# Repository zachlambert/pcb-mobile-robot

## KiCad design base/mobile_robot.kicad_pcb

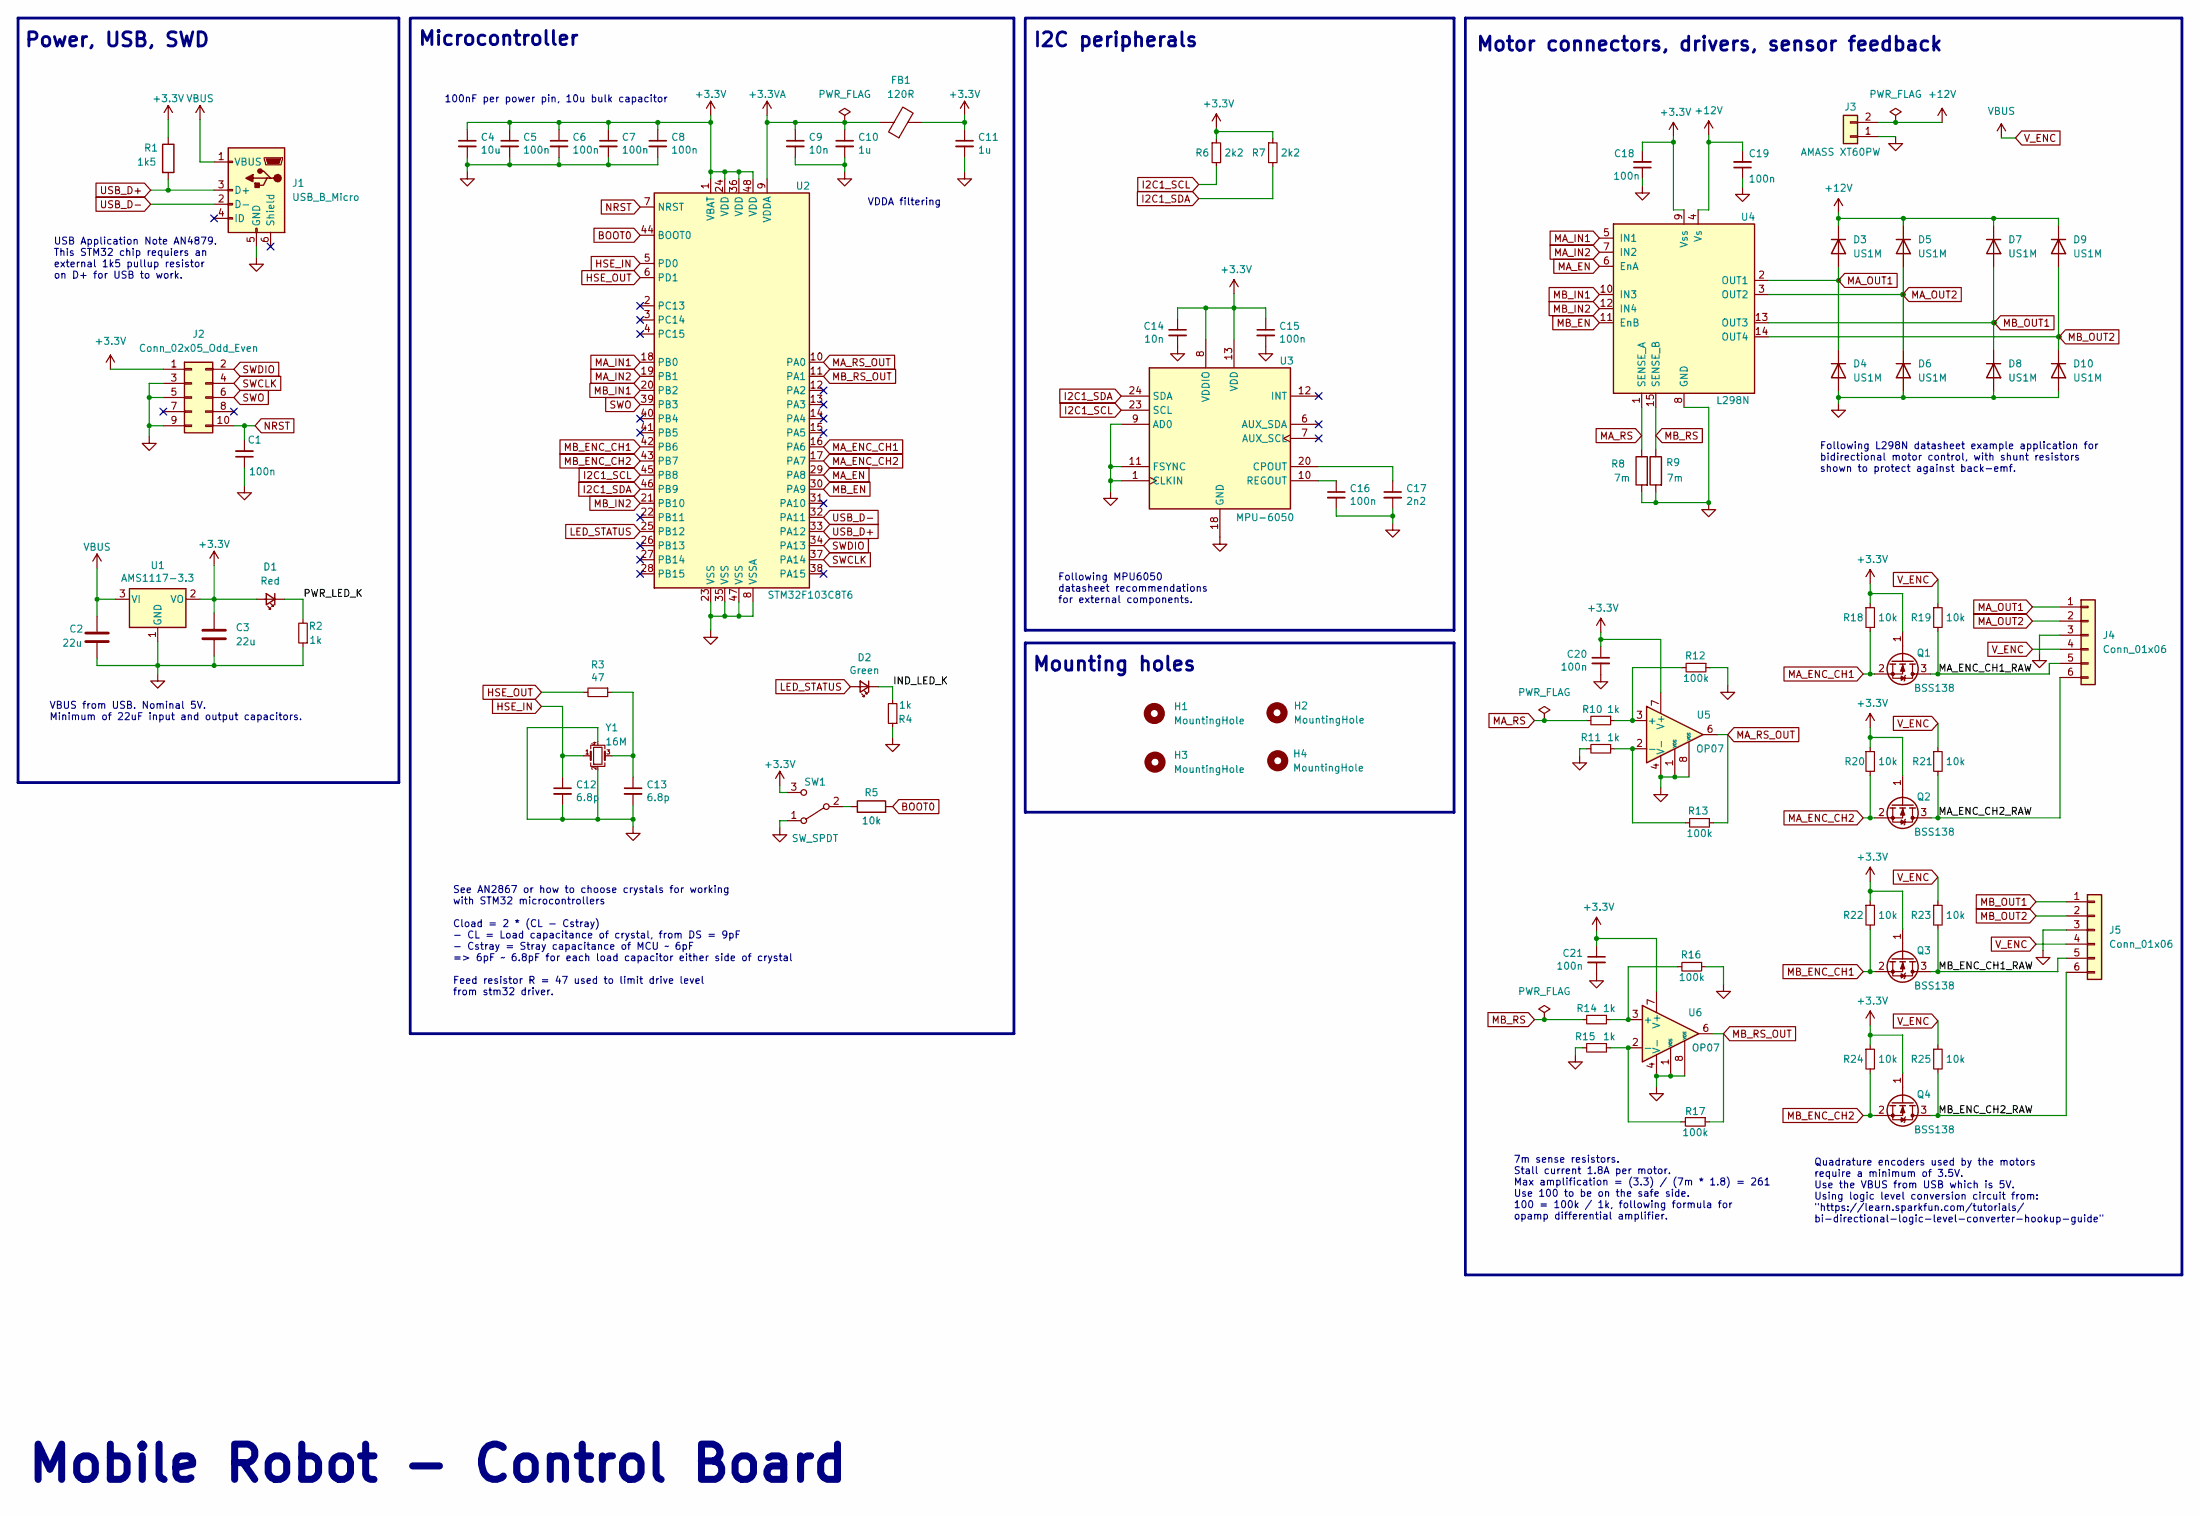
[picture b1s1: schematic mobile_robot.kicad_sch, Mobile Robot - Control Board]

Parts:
C1, C5, C6, C7, C8, C15, C16, C18, C19, C20, C21: 100n; C_0402_1005Metric
C2, C3: 22u; C_0805_2012Metric
C4: 10u; C_0603_1608Metric
C9, C14: 10n; C_0402_1005Metric
C10, C11: 1u; C_0402_1005Metric
C12, C13: 6.8p; C_0402_1005Metric
C17: 2n2; C_0402_1005Metric
D1: Red; D_0603_1608Metric
D2: Green; D_0603_1608Metric
D3, D4, D5, D6, D7, D8, D9, D10: US1M; D_SMA
FB1: 120R; L_0603_1608Metric
H1, H2, H3, H4: MountingHole; MountingHole_3.2mm_M3
J1: USB_B_Micro; USB_Micro-B_Molex_47346-0001
J2: Conn_02x05_Odd_Even; PinHeader_2x05_P2.54mm_Vertical
J3: AMASS XT60PW; AMASS_XT60PW-M
J4, J5: Conn_01x06; PinHeader_1x06_P2.54mm_Vertical
Q1, Q2, Q3, Q4: BSS138; SOT-23
R1: 1k5; R_0402_1005Metric
R2, R4, R10, R11, R14, R15: 1k; R_0402_1005Metric
R3: 47; R_0402_1005Metric
R5, R18, R19, R20, R21, R22, R23, R24, R25: 10k; R_0402_1005Metric
R6, R7: 2k2; R_0402_1005Metric
R8, R9: 7m; R_2512_6332Metric
R12, R13, R16, R17: 100k; R_0402_1005Metric
SW1: SW_SPDT; SW_SPDT_PCM12
U1: AMS1117-3.3; SOT-223-3_TabPin2
U2: STM32F103C8T6; LQFP-48_7x7mm_P0.5mm
U3: MPU-6050; InvenSense_QFN-24_4x4mm_P0.5mm
U4: L298N; TO-220-15_P2.54x2.54mm_StaggerOdd_Lead4.58mm_Vertical
U5, U6: OP07; SOIC-8_3.9x4.9mm_P1.27mm
Y1: 16M; Crystal_SMD_3225-4Pin_3.2x2.5mm

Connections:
+3.3VA: C9.1, C10.1, FB1.1, U2.9 (VDDA)
+3V3: C3.1, C4.1, C5.1, C6.1, C7.1, C8.1, C11.1, C14.1, C15.1, C18.2, C20.1, C21.1, D1.2 (A), FB1.2, J2.1, Q1.1 (G), Q2.1 (G), Q3.1 (G), Q4.1 (G), R1.1, R6.1, R7.1, R18.1, R20.1, R22.1, R24.1, SW1.3 (C), U1.2 (VO), U2.1 (VBAT), U2.24 (VDD), U2.36 (VDD), U2.48 (VDD), U3.8 (VDDIO), U3.13 (VDD), U4.9 (Vss), U5.7 (V+), U6.7 (V+)
+12V: C19.2, D3.1 (K), D5.1 (K), D7.1 (K), D9.1 (K), J3.2, U4.4 (Vs)
/IND_LED_K: D2.1 (K), R4.2
/MA_ENC_CH1_RAW: J4.5, Q1.3 (D), R19.2
/MA_ENC_CH2_RAW: J4.6, Q2.3 (D), R21.2
/MB_ENC_CH1_RAW: J5.5, Q3.3 (D), R23.2
/MB_ENC_CH2_RAW: J5.6, Q4.3 (D), R25.2
/PWR_LED_K: D1.1 (K), R2.2
BOOT0: R5.2, U2.44 (BOOT0)
GND: C1.1, C2.2, C3.2, C4.2, C5.2, C6.2, C7.2, C8.2, C9.2, C10.2, C11.2, C12.2, C13.2, C14.2, C15.2, C16.2, C17.2, C18.1, C19.1, C20.2, C21.2, D4.2 (A), D6.2 (A), D8.2 (A), D10.2 (A), J1.5 (GND), J2.3, J2.5, J2.9, J3.1, J4.3, J5.3, R2.1, R4.1, R8.2, R9.2, R11.2, R12.1, R15.2, R16.1, SW1.1 (A), U1.1 (GND), U2.8 (VSSA), U2.23 (VSS), U2.35 (VSS), U2.47 (VSS), U3.1 (CLKIN), U3.9 (AD0), U3.11 (FSYNC), U3.18 (GND), U4.8 (GND), U5.1 (VOS), U5.4 (V-), U5.8 (VOS), U6.1 (VOS), U6.4 (V-), U6.8 (VOS), Y1.2, Y1.4
HSE_IN: C12.1, U2.5 (PD0), Y1.1
HSE_OUT: R3.2, U2.6 (PD1)
I2C1_SCL: R6.2, U2.45 (PB8), U3.23 (SCL)
I2C1_SDA: R7.2, U2.46 (PB9), U3.24 (SDA)
LED_STATUS: D2.2 (A), U2.25 (PB12)
MA_EN: U2.29 (PA8), U4.6 (EnA)
MA_ENC_CH1: Q1.2 (S), R18.2, U2.16 (PA6)
MA_ENC_CH2: Q2.2 (S), R20.2, U2.17 (PA7)
MA_IN1: U2.18 (PB0), U4.5 (IN1)
MA_IN2: U2.19 (PB1), U4.7 (IN2)
MA_OUT1: D3.2 (A), D4.1 (K), J4.1, U4.2 (OUT1)
MA_OUT2: D5.2 (A), D6.1 (K), J4.2, U4.3 (OUT2)
MA_RS: R8.1, R10.2, U4.1 (SENSE_A)
MA_RS_OUT: R13.1, U2.10 (PA0), U5.6
MB_EN: U2.30 (PA9), U4.11 (EnB)
MB_ENC_CH1: Q3.2 (S), R22.2, U2.42 (PB6)
MB_ENC_CH2: Q4.2 (S), R24.2, U2.43 (PB7)
MB_IN1: U2.20 (PB2), U4.10 (IN3)
MB_IN2: U2.21 (PB10), U4.12 (IN4)
MB_OUT1: D7.2 (A), D8.1 (K), J5.1, U4.13 (OUT3)
MB_OUT2: D9.2 (A), D10.1 (K), J5.2, U4.14 (OUT4)
MB_RS: R9.1, R14.2, U4.15 (SENSE_B)
MB_RS_OUT: R17.1, U2.11 (PA1), U6.6
NRST: C1.2, J2.10, U2.7 (NRST)
unnamed: C13.1, R3.1, Y1.3
unnamed: C16.1, U3.10 (REGOUT)
unnamed: C17.1, U3.20 (CPOUT)
unnamed: R5.1, SW1.2 (B)
unnamed: R10.1, R12.2, U5.3 (+)
unnamed: R11.1, R13.2, U5.2 (-)
unnamed: R14.1, R16.2, U6.3 (+)
unnamed: R15.1, R17.2, U6.2 (-)
SWCLK: J2.4, U2.37 (PA14)
SWDIO: J2.2, U2.34 (PA13)
SWO: J2.6, U2.39 (PB3)
USB_D+: J1.3 (D+), R1.2, U2.33 (PA12)
USB_D-: J1.2 (D-), U2.32 (PA11)
V_ENC: C2.1, J1.1 (VBUS), J4.4, J5.4, R19.1, R21.1, R23.1, R25.1, U1.3 (VI)

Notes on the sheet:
Motor connectors, drivers, sensor feedback
VDDA filtering
Following MPU6050 datasheet recommendations for external components.
I2C peripherals
Mounting holes
100nF per power pin, 10u bulk capacitor
Microcontroller
7m sense resistors. Stall current 1.8A per motor. Max amplification = (3.3) / (7m * 1.8) = 261 Use 100 to be on the safe side. 100 = 100k / 1k, following formula for opamp differential amplifier.
Mobile Robot - Control Board
Power, USB, SWD
Following L298N datasheet example application for bidirectional motor control, with shunt resistors shown to protect against back-emf.
See AN2867 or how to choose crystals for working with STM32 microcontrollers Cload = 2 * (CL - Cstray) - CL = Load capacitance of crystal, from DS = 9pF - Cstray = Stray capacitance of MCU ~ 6pF => 6pF ~ 6.8pF for each load capacitor either side of crystal Feed resistor R = 47 used to limit drive l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
VBUS from USB. Nominal 5V. Minimum of 22uF input and output capacitors.
USB Application Note AN4879. This STM32 chip requiers an external 1k5 pullup resistor on D+ for USB to work.
Quadrature encoders used by the motors require a minimum of 3.5V. Use the VBUS from USB which is 5V. Using logic level conversion circuit from: "https://learn.sparkfun.com/tutorials/ bi-directional-logic-level-converter-hookup-guide"

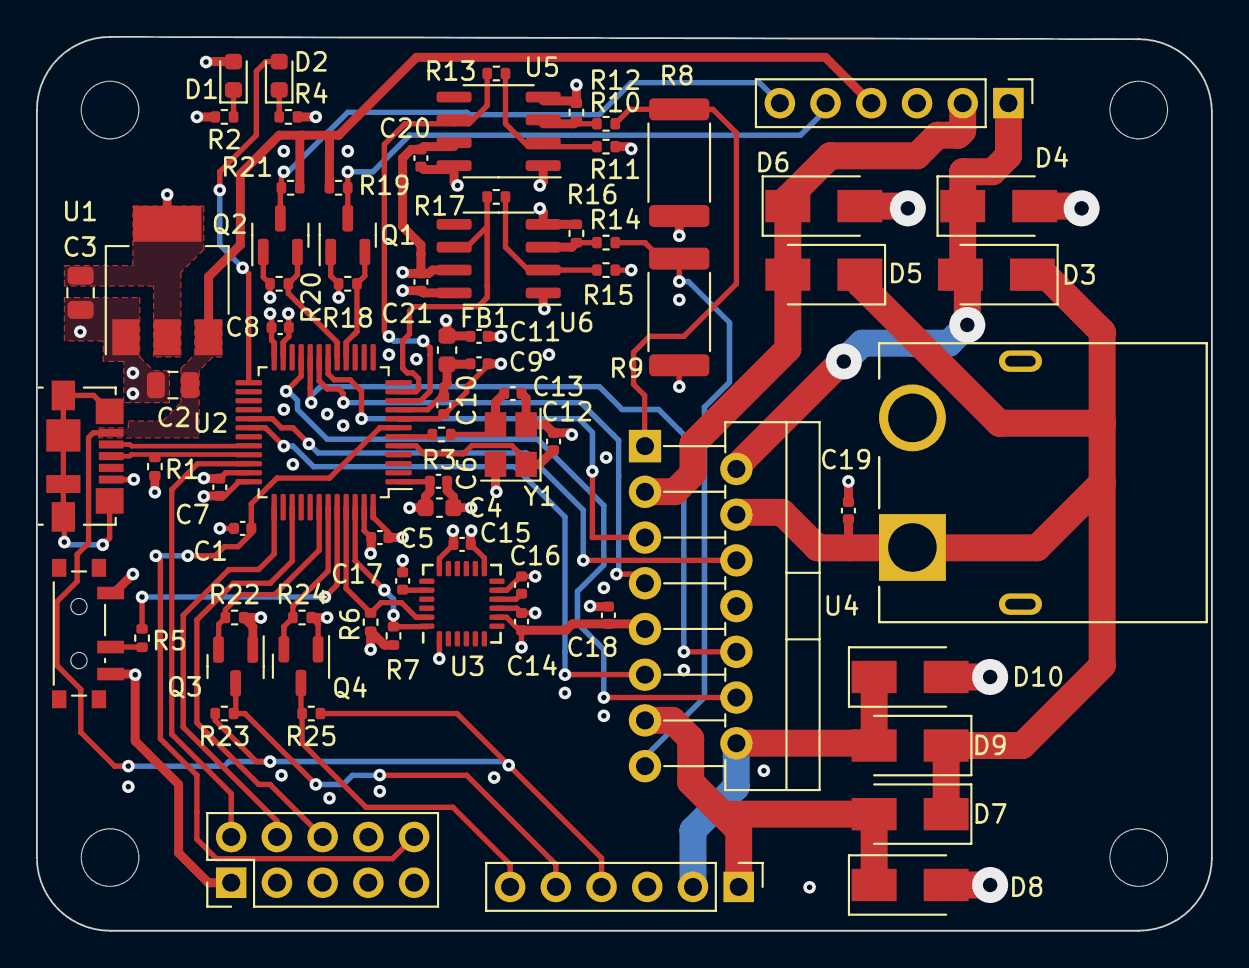
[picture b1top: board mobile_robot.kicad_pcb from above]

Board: 4 copper layers, 65.3 x 49.7 mm, 78 parts (0 on the bottom side), 49 nets.

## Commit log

2022-08-02 Finished schematic and initial component placement on pcb
2022-08-05 Pretty much finished pcb layout and routing
2022-08-05 Did usb differential pair properly
2022-08-06 Finished PCB
